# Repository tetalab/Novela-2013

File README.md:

Novela-2013
===========

Novela 2013 content

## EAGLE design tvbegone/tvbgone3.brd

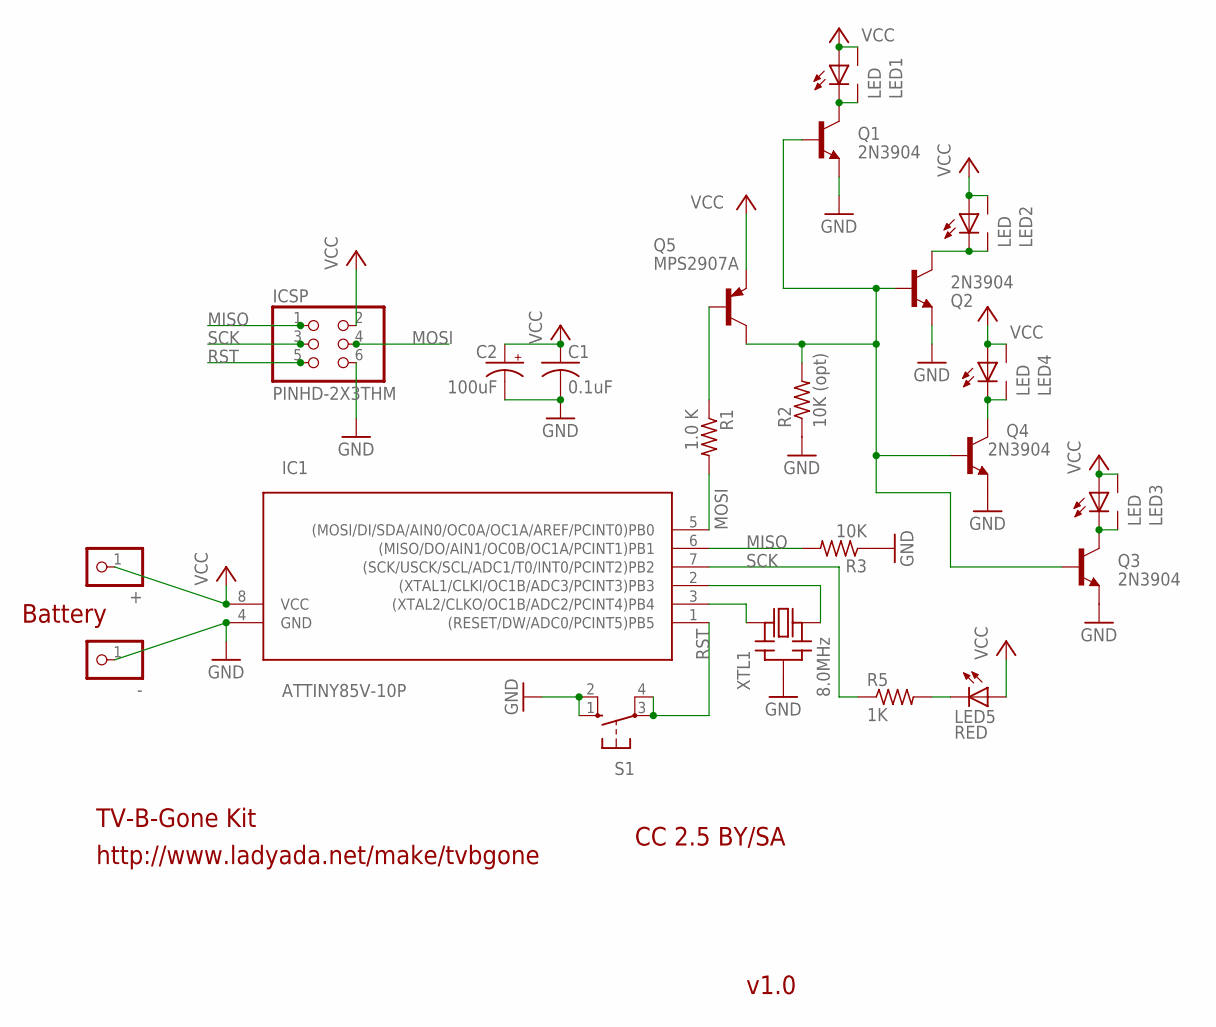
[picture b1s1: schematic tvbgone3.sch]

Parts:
+: PINHD-1X1; 1X01
-: PINHD-1X1; 1X01
C1: 0.1uF; C025-025X050
C2: 100uF; E2,5-5
IC1: ATTINY85V-10P; DIL08
ICSP: PINHD-2X3THM; ISP6
LED1, LED2, LED3, LED4: LED; 5MM-SIDE
LED5: RED; LED3MM
Q1, Q2, Q3, Q4: 2N3904; TO92-EZ
Q5: MPS2907A; TO92-CBE
R1: 1.0 K; 0207/10
R2: 10K (opt); 0207/10
R3: 10K; 0207/10
R5: 1K; 0207/10
S1: 10-XX; B3F-10XX
XTL1: 8.0MHz; CERM_OSC

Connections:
GND: -.1, C1.2, C2.-, IC1.4 (GND), ICSP.6, Q1.3 (E), Q2.3 (E), Q3.3 (E), Q4.3 (E), R2.1, R3.1, S1.1 (S), S1.2 (S1), XTL1.P$2 (GND)
MISO: IC1.6 ((MISO/DO/AIN1/OC0B/OC1A/PCINT1)PB1), ICSP.1, R3.2
MOSI: IC1.5 ((MOSI/DI/SDA/AIN0/OC0A/OC1A/AREF/PCINT0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), ICSP.4, R1.2
unnamed: IC1.3 ((XTAL2/CLKO/OC1B/ADC2/PCINT4)PB4), XTL1.P$1 (IN)
unnamed: IC1.2 ((XTAL1/CLKI/OC1B/ADC3/PCINT3)PB3), XTL1.P$3 (OUT)
unnamed: LED5.K (C), R5.2
unnamed: Q5.B, R1.1
unnamed: LED4.K (C), LED4.K2 (C1), Q4.1 (C)
unnamed: LED2.K (C), LED2.K2 (C1), Q2.1 (C)
unnamed: LED3.K (C), LED3.K2 (C1), Q3.1 (C)
unnamed: Q1.2 (B), Q2.2 (B), Q3.2 (B), Q4.2 (B), Q5.C, R2.2
unnamed: LED1.K (C), LED1.K2 (C1), Q1.1 (C)
RST: IC1.1 ((RESET/DW/ADC0/PCINT5)PB5), ICSP.5, S1.3, S1.4 (P1)
SCK: IC1.7 ((SCK/USCK/SCL/ADC1/T0/INT0/PCINT2)PB2), ICSP.3, R5.1
VCC: +.1, C1.1, C2.+, IC1.8 (VCC), ICSP.2, LED1.A, LED1.A2 (A1), LED2.A, LED2.A2 (A1), LED3.A, LED3.A2 (A1), LED4.A, LED4.A2 (A1), LED5.A, Q5.E

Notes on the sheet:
http://www.ladyada.net/make/tvbgone
TV-B-Gone Kit
v1.0
CC 2.5 BY/SA
Battery

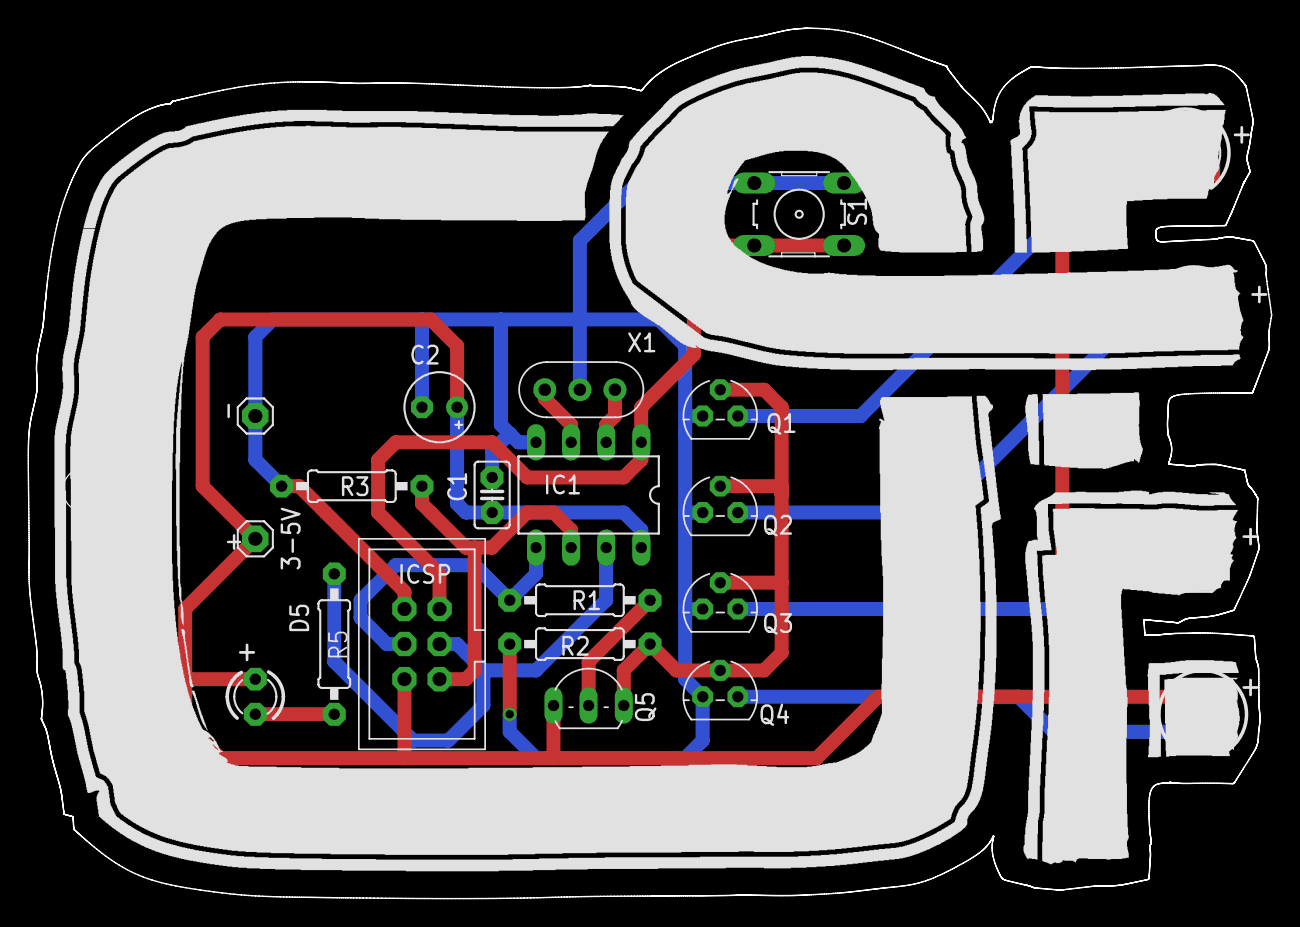
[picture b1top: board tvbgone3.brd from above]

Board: 2 copper layers, 90.0 x 63.0 mm, 22 parts (0 on the bottom side), 15 nets.

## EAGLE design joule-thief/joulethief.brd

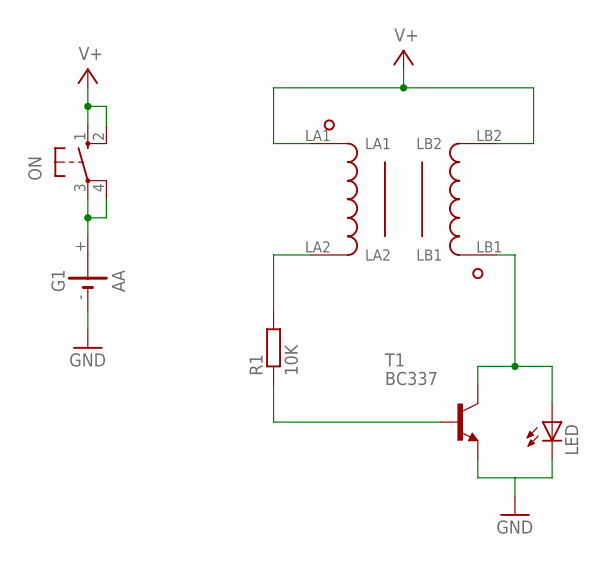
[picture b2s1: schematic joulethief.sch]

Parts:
G1: AA; AA-HOLDER
LED: LED5MM
ON: 10-XX; B3F-10XX
R1: 10K; 0207/10
T1: BC337; TO92
U$1: COIL-BEAD; BEAD-22-13.8-6.4

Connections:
GND: G1.-, LED.K (C), T1.1 (E)
unnamed: G1.+, ON.3, ON.4 (P1)
unnamed: R1.2, U$1.LA2
unnamed: R1.1, T1.2 (B)
unnamed: LED.A, T1.3 (C), U$1.LB1
V+: ON.1 (S), ON.2 (S1), U$1.LA1, U$1.LB2

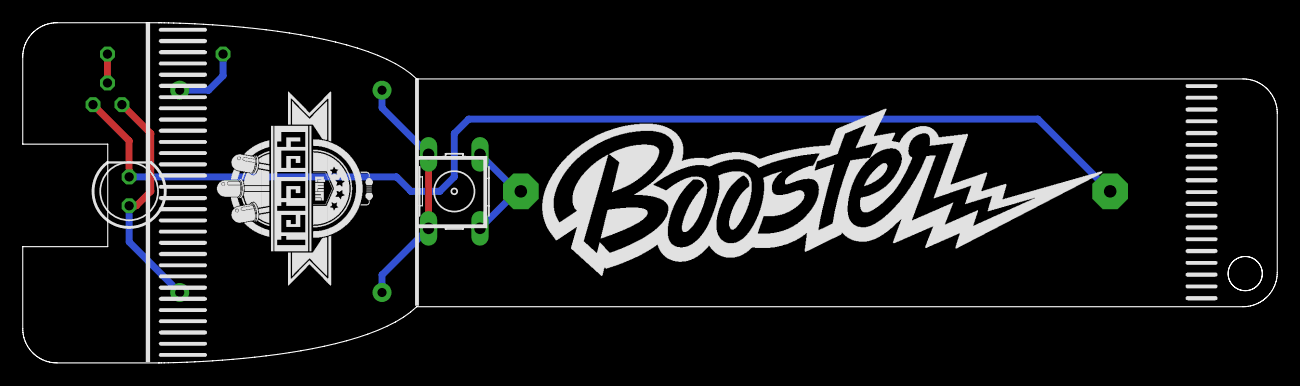
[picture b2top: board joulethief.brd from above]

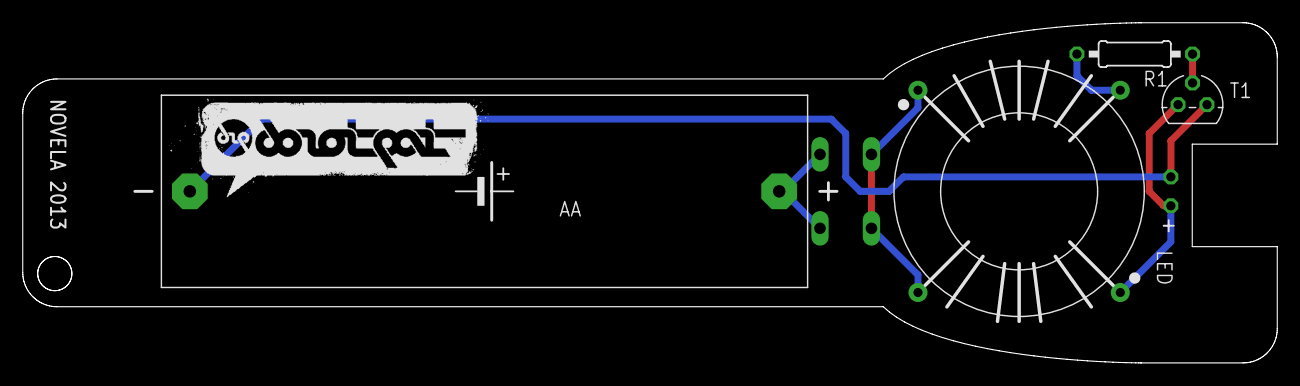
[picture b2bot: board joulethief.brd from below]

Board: 2 copper layers, 110.3 x 29.9 mm, 6 parts (4 on the bottom side), 6 nets.

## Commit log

2014-09-17 Ajout git ignore
2014-09-17 Joule theft design added
2014-09-17 Off (TV be Gone) design added
2020-10-15 Add documentation
